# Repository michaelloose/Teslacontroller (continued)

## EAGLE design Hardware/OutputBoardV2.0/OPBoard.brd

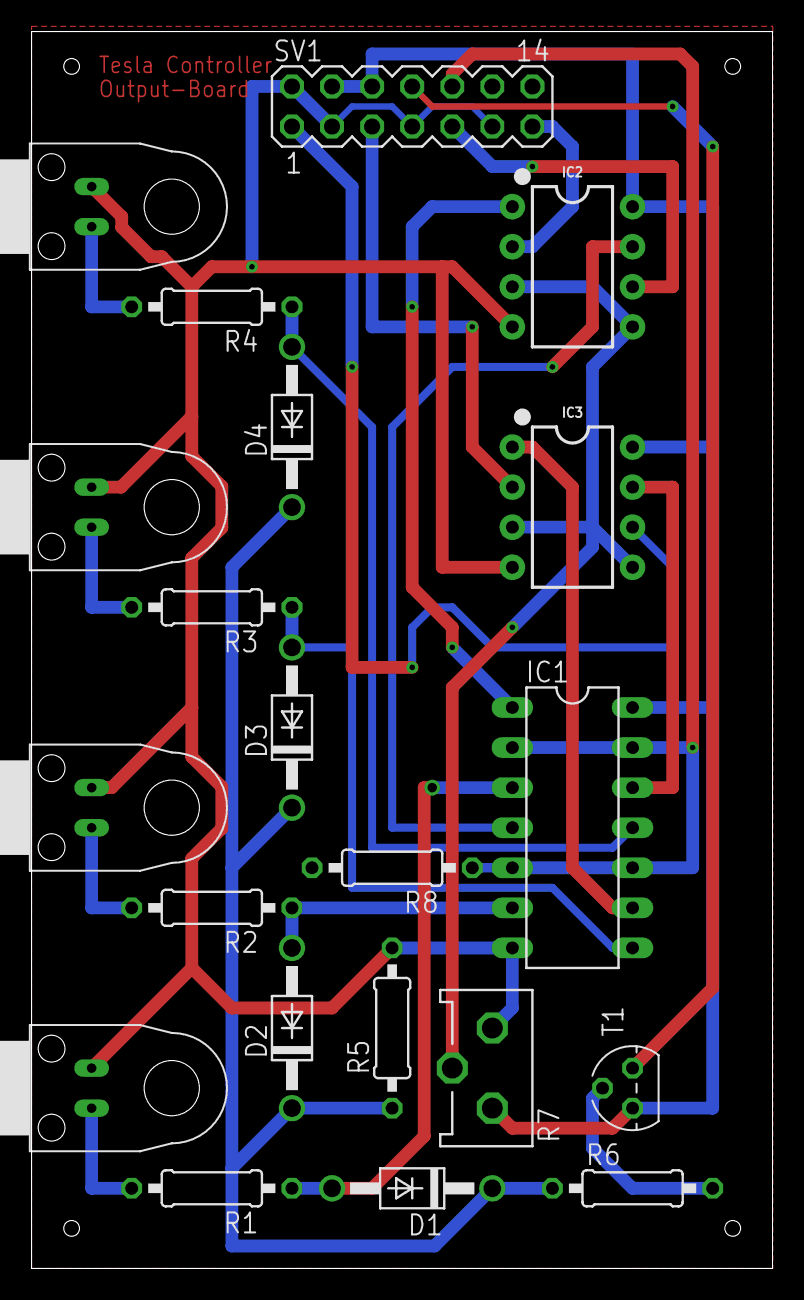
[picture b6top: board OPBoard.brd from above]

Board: 2 copper layers, 47.0 x 78.4 mm, 21 parts (0 on the bottom side), 23 nets.

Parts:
D1, D2, D3, D4: 1N4004; DO41-10
IC1: 74AC08N; DIL14
IC2, IC3: OP-AMP; DIP08
R1, R2, R3, R4: 1k; 0207/10
R5, R8: 10k; 0207/10
R6: 0207/10
R7: ECP10P
SV1: MA07-2
T1: BC547; TO92
U$1, U$2, U$3, U$4: IF_XX_TRANSMITTER; IF_XX

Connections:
ENABLE: IC1.2, IC1.5, IC1.10, IC1.13, R8.1, SV1.10
GND: IC1.7, IC2.4, IC3.4, R5.2, R7.E, R8.2, SV1.2, SV1.3, SV1.7, SV1.11, U$1.K, U$2.K, U$3.K, U$4.K
LED: SV1.8, T1.1
unnamed: R1.2, U$1.A
unnamed: R2.2, U$2.A
unnamed: R3.2, U$3.A
unnamed: R4.2, U$4.A
unnamed: D1.A, IC1.3, R1.1
unnamed: D2.A, IC1.6, R2.1
unnamed: D3.A, IC1.8, R3.1
unnamed: D4.A, IC1.11, R4.1
unnamed: D1.C, D2.C, D3.C, D4.C, R5.1, R6.1
unnamed: R6.2, T1.2
unnamed: IC2.2, SV1.13
unnamed: IC1.1, IC2.1
unnamed: IC1.4, IC2.7
unnamed: IC1.9, IC3.1
unnamed: IC1.12, IC3.7
unnamed: IC2.3, IC2.5, IC3.3, IC3.5, R7.S
unnamed: IC2.6, SV1.9
unnamed: IC3.2, SV1.5
unnamed: IC3.6, SV1.1
VCC: IC1.14, IC2.8, IC3.8, R7.A, SV1.4, SV1.6, T1.3

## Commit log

2019-03-20 Verlagern des Logos in den Flash Speicher Implementierung des Task Managers Einführung der Tasten Bekannter Fehler: Encoder Rad muss gedreht werden bevor andere Tasten erkannt werden.
2019-03-22 Grundbild Menü funktioniert jetzt
2019-04-01 PCF8574 wird nun mit eigenem Code ausgelesen, bessere Performance Speichern ist möglich Erstellen der 24V SSTC
2019-04-02 Fertigstellung der SSTC Kleinere Bugfixes im UI
2019-04-19 Erschaffen der Schnittstellen für den Mediaplayer
2019-04-23 Fertigstellung der Implementation der Dateiauswahl und der Playtaste in der UI
2019-04-25 Menu Completed
2019-05-01 Array einlesen hinzugefügt
2019-05-02 Array erstellen
2019-05-08 Auf SdFat.h umgestellt
2019-05-08 Sdfat.h eingesetzt
2019-05-09 Software
2019-05-09 SSTC Frontpanel design
2019-05-10 Liste und SD wechsel fertig
2019-05-10 Header Mediaplayer
2019-05-11 midi Ausgabe eingefügt
2019-05-13 Display funktioniert nun mit SD Karte gemeinsam
2019-05-16 New File to recieve MIDI Input and throw out unwanted Bytes
2019-05-20 Media Player läuft, Einstellungen werden in der pcf8575 Datei verwaltet (Funktioniert nicht)
2019-05-20 Bugs from previous version fixed
2019-05-21 Making test file for DSP communication, minor fixes
2019-05-22 Implemented Communication to the DSP
2019-05-24 MIDI Eingangsschnittstelle fertig, Boards hinzugefügt
2019-05-25 DoubleInputBoard
2019-05-25 InputBoard überarbeitet, pinout bereitgestellt
2019-05-26 Added Mainboard
2019-05-27 Letzte Änderungen an Netzteil, OP und IP Board
2019-05-27 Minor Board Fixes
2019-05-29 Added Coil Type Support for up tu 6 different types
2019-05-30 Include too deeply Fehler behoben
2019-05-31 Minor Bugfixes, Implemented PitchBend, Implemented SongControl via MIDI
2019-06-03 Added MIDI Auto Distribute Functionality
2019-06-03 Minor Updates
2019-06-05 Minor fixes
2019-06-07 Druckfunktion hinzugefügt
    Druckfunktion hinzugefügt, muss noch in ui.cpp implementiert werden
2019-06-09 Added Output enable, Added Utility Screen
2019-06-10 SD Bugfix
    Druckfunktion fertig, SD läuft,
    Drehsinn geändert
2019-06-11 Bugfixes
2019-06-12 Analog Input Implemented
